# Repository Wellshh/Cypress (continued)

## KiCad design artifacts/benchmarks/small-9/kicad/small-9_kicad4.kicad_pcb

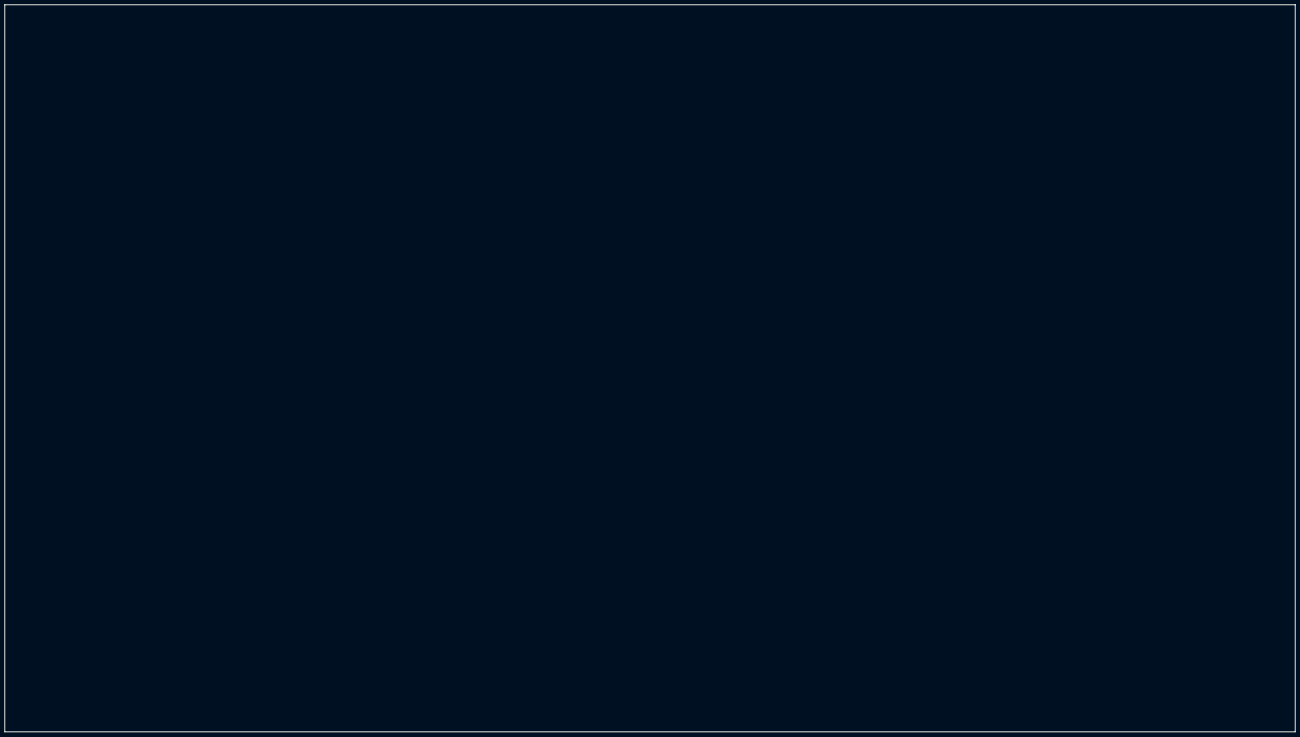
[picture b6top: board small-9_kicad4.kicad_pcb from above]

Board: 2 copper layers, 564.1 x 317.8 mm, 476 parts (0 on the bottom side), 253 nets, no tracks yet.

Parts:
C0: C0; 320-2241-000
C1: C1; 320-2241-000
C2: C2; 320-2241-000
C3: C3; 320-2241-000
C4: C4; 320-2241-000
C5: C5; 320-2241-000
C6: C6; 320-2241-000
C7: C7; 320-2241-000
C8: C8; 320-2241-000
C9: C9; 320-2241-000
C10: C10; 320-2241-000
C11: C11; 320-2241-000
C12: C12; 320-2241-000
C13: C13; 320-2241-000
C14: C14; 032-2145-000
C15: C15; 032-2145-000
C16: C16; 032-2145-000
C17: C17; 032-2145-000
C18: C18; 032-2145-000
C19: C19; 032-2145-000
C20: C20; 032-2145-000
C21: C21; 032-2145-000
C22: C22; 032-2145-000
C23: C23; 032-2145-000
C24: C24; 032-2145-000
C25: C25; 032-2145-000
C26: C26; 032-2145-000
C27: C27; 032-2145-000
C28: C28; 032-2145-000
C29: C29; 032-2145-000
C30: C30; 032-2145-000
C31: C31; 032-2145-000
C32: C32; 032-2145-000
C33: C33; 032-2145-000
C34: C34; 032-2145-000
C35: C35; 032-2145-000
C36: C36; 032-2145-000
C37: C37; 032-2145-000
C38: C38; 032-2145-000
C39: C39; 032-2145-000
C40: C40; 032-2145-000
C41: C41; 032-2145-000
C42: C42; 032-2145-000
C43: C43; 032-2145-000
C44: C44; 032-2145-000
C45: C45; 032-2145-000
C46: C46; 032-2145-000
C47: C47; 032-2145-000
C48: C48; 032-2145-000
C49: C49; 032-2145-000
C50: C50; 032-2145-000
C51: C51; 032-2145-000
C52: C52; 032-2145-000
C53: C53; 032-2145-000
C54: C54; 032-2145-000
C55: C55; 032-2145-000
C56: C56; 032-2145-000
C57: C57; 032-2145-000
C58: C58; 032-2145-000
C59: C59; 032-2145-000
C60: C60; 032-2145-000
C61: C61; 032-2145-000
C62: C62; 032-2145-000
C63: C63; 032-2145-000
C64: C64; 032-2145-000
C65: C65; 032-2145-000
C66: C66; 032-2145-000
C67: C67; 032-2145-000
C68: C68; 032-2145-000
C69: C69; 032-2145-000
C70: C70; 032-2145-000
C71: C71; 032-2145-000
C72: C72; 032-2145-000
C73: C73; 032-2145-000
C74: C74; 032-2145-000
C75: C75; 032-2145-000
C76: C76; 032-2145-000
C77: C77; 032-2145-000
C78: C78; 032-2145-000
C79: C79; 032-2145-000
C80: C80; 032-2145-000
C81: C81; 032-2145-000
C82: C82; 032-2145-000
C83: C83; 032-2145-000
C84: C84; 032-2145-000
C85: C85; 032-2145-000
C86: C86; 032-2145-000
C87: C87; 032-2145-000
C88: C88; 032-2145-000
C89: C89; 032-2145-000
C90: C90; 032-2145-000
C91: C91; 032-2145-000
C92: C92; 032-2145-000
C93: C93; 032-2145-000
C94: C94; 032-2145-000
C95: C95; 032-2145-000
C96: C96; 032-2145-000
C97: C97; 032-2145-000
C98: C98; 032-2145-000
C99: C99; 032-2145-000
C100: C100; 032-2145-000
C101: C101; 032-2145-000
C102: C102; 032-2145-000
C103: C103; 032-2145-000
C104: C104; 032-2145-000
C105: C105; 032-2145-000
C106: C106; 032-2145-000
C107: C107; 032-2145-000
C108: C108; 032-2145-000
C109: C109; 032-2145-000
C110: C110; 032-2145-000
C111: C111; 032-2145-000
C112: C112; 032-2145-000
C113: C113; 032-2145-000
C114: C114; 032-2145-000
C115: C115; 032-2145-000
C116: C116; 032-2145-000
C117: C117; 032-2145-000
C118: C118; 032-2145-000
C119: C119; 032-2145-000
C120: C120; 032-2145-000
C121: C121; 032-2145-000
C122: C122; 032-2145-000
C123: C123; 032-2145-000
C124: C124; 032-2145-000
C125: C125; 032-2145-000
C126: C126; 080-2248-000
C127: C127; 080-2248-000
C128: C128; 080-2248-000
C129: C129; 080-2248-000
C130: C130; 080-2248-000
C131: C131; 080-2248-000
C132: C132; 080-2248-000
C133: C133; 080-2248-000
C134: C134; 080-2248-000
C135: C135; 080-2248-000
C136: C136; 080-2248-000
C137: C137; 080-2248-000
C138: C138; 080-2248-000
C139: C139; 080-2248-000
C140: C140; 130-1487-000
C141: C141; 130-1487-000
C142: C142; 130-1487-000
C143: C143; 130-1487-000
C144: C144; 130-1487-000
C145: C145; 130-1487-000
C146: C146; 130-1487-000
C147: C147; 130-1487-000
C148: C148; 130-1487-000
C149: C149; 130-1487-000
C150: C150; 130-1487-000
C151: C151; 130-1487-000
C152: C152; 130-1487-000
C153: C153; 130-1487-000
C154: C154; 130-1487-000
C155: C155; 130-1487-000
C156: C156; 130-1487-000
C157: C157; 130-1487-000
C158: C158; 130-1487-000
C159: C159; 130-1487-000
C160: C160; 130-1487-000
C161: C161; 130-1487-000
C162: C162; 130-1487-000
C163: C163; 130-1487-000
C164: C164; 130-1487-000
C165: C165; 130-1487-000
C166: C166; 130-1487-000
C167: C167; 130-1487-000
C168: C168; 130-1487-000
C169: C169; 130-1487-000
C170: C170; 130-1487-000
C171: C171; 130-1487-000
C172: C172; 130-1487-000
C173: C173; 130-1487-000
C174: C174; 130-1487-000
C175: C175; 130-1487-000
C176: C176; 130-1487-000
C177: C177; 130-1487-000
C178: C178; 130-1487-000
C179: C179; 130-1487-000
C180: C180; 130-1487-000
C181: C181; 130-1487-000
C182: C182; 130-1487-000
C183: C183; 130-1487-000
C184: C184; 130-1487-000
C185: C185; 130-1487-000
C186: C186; 130-1487-000
C187: C187; 130-1487-000
C188: C188; 130-1487-000
C189: C189; 130-1487-000
C190: C190; 130-1487-000
C191: C191; 130-1487-000
C192: C192; 130-1487-000
C193: C193; 130-1487-000
C194: C194; 130-1487-000
C195: C195; 130-1487-000
C196: C196; 130-1487-000
C197: C197; 130-1487-000
C198: C198; 130-1487-000
C199: C199; 130-1487-000
C200: C200; 130-1487-000
C201: C201; 130-1487-000
C202: C202; 130-1487-000
C203: C203; 130-1487-000
C204: C204; 130-1487-000
C205: C205; 130-1487-000
C206: C206; 130-1487-000
C207: C207; 130-1487-000
C208: C208; 130-1487-000
C209: C209; 130-1487-000
C210: C210; 130-1487-000
C211: C211; 130-1487-000
C212: C212; 130-1487-000
C213: C213; 130-1487-000
C214: C214; 130-1487-000
C215: C215; 130-1487-000
C216: C216; 130-1487-000
C217: C217; 130-1487-000
C218: C218; 130-1487-000
C219: C219; 130-1487-000
C220: C220; 130-1487-000
C221: C221; 130-1487-000
C222: C222; 130-1487-000
C223: C223; 130-1487-000
C224: C224; 032-0863-000
C225: C225; 195-0004-000
C226: C226; 195-0004-000
C227: C227; 195-0004-000
C228: C228; 195-0004-000
C229: C229; 195-0004-000
C230: C230; 195-0004-000
C231: C231; 195-0004-000
C232: C232; 195-0004-000
C233: C233; 195-0004-000
C234: C234; 195-0004-000
C235: C235; 195-0004-000
C236: C236; 195-0004-000
C237: C237; 195-0004-000
C238: C238; 195-0004-000
C239: C239; 195-0004-000
C240: C240; 195-0004-000
C241: C241; 195-0004-000
C242: C242; 195-0004-000
C243: C243; 195-0004-000
C244: C244; 195-0004-000
C245: C245; 195-0004-000
C246: C246; 195-0004-000
C247: C247; 195-0004-000
C248: C248; 195-0004-000
C249: C249; 195-0004-000
C250: C250; 195-0004-000
C251: C251; 195-0004-000
C252: C252; 195-0004-000
C253: C253; 195-0004-000
C254: C254; 195-0004-000
C255: C255; 195-0004-000
C256: C256; 195-0004-000
C257: C257; 195-0004-000
C258: C258; 195-0004-000
C259: C259; 195-0004-000
C260: C260; 195-0004-000
C261: C261; 195-0004-000
C262: C262; 195-0004-000
C263: C263; 195-0004-000
C264: C264; 195-0004-000
C265: C265; 195-0004-000
C266: C266; 195-0004-000
C267: C267; 195-0004-000
C268: C268; 195-0004-000
C269: C269; 195-0004-000
C270: C270; 195-0004-000
C271: C271; 195-0004-000
C272: C272; 195-0004-000
C273: C273; 195-0004-000
C274: C274; 195-0004-000
C275: C275; 195-0004-000
C276: C276; 195-0004-000
C277: C277; 195-0004-000
C278: C278; 195-0004-000
C279: C279; 195-0004-000
C280: C280; 195-0004-000
C281: C281; 195-0005-000
C282: C282; 195-0005-000
C283: C283; 195-0005-000
C284: C284; 195-0005-000
C285: C285; 195-0005-000
C286: C286; 195-0005-000
C287: C287; 195-0005-000
C288: C288; 195-0005-000
C289: C289; 195-0005-000
C290: C290; 195-0005-000
C291: C291; 195-0005-000
C292: C292; 195-0005-000
C293: C293; 195-0005-000
C294: C294; 195-0005-000
C295: C295; 195-0005-000
C296: C296; 195-0005-000
C297: C297; 195-0005-000
C298: C298; 195-0005-000
C299: C299; 195-0005-000
C300: C300; 195-0005-000
C301: C301; 195-0005-000
C302: C302; 195-0005-000
C303: C303; 195-0005-000
C304: C304; 195-0005-000
C305: C305; 195-0005-000
C306: C306; 195-0005-000
C307: C307; 195-0005-000
C308: C308; 195-0005-000
C309: C309; 195-0005-000
C310: C310; 195-0005-000
C311: C311; 195-0005-000
C312: C312; 195-0005-000
C313: C313; 195-0005-000
C314: C314; 195-0005-000
C315: C315; 195-0005-000
C316: C316; 195-0005-000
C317: C317; 195-0005-000
C318: C318; 195-0005-000
C319: C319; 195-0005-000
C320: C320; 195-0005-000
C321: C321; 195-0005-000
C322: C322; 195-0005-000
C323: C323; 195-0005-000
C324: C324; 195-0005-000
C325: C325; 195-0005-000
C326: C326; 195-0005-000
C327: C327; 195-0005-000
C328: C328; 195-0005-000
C329: C329; 195-0005-000
C330: C330; 195-0005-000
C331: C331; 195-0005-000
C332: C332; 195-0005-000
C333: C333; 195-0005-000
C334: C334; 195-0005-000
C335: C335; 195-0005-000
C336: C336; 195-0005-000
C337: C337; 032-0863-000
C338: C338; 032-0863-000
C339: C339; 032-0863-000
C340: C340; 032-0863-000
C341: C341; 032-0863-000
C342: C342; 032-0863-000
C343: C343; 032-0863-000
C344: C344; 032-0863-000
C345: C345; 032-0863-000
C346: C346; 032-0863-000
C347: C347; 032-0863-000
C348: C348; 032-0863-000
C349: C349; 032-0863-000
C350: C350; 032-0863-000
C351: C351; 032-0863-000
C352: C352; 032-0863-000
C353: C353; 032-0863-000
C354: C354; 032-0863-000
C355: C355; 032-0863-000
C356: C356; 032-0863-000
C357: C357; 032-0863-000
C358: C358; 032-0863-000
C359: C359; 032-0863-000
C360: C360; 032-0863-000
C361: C361; 032-0863-000
C362: C362; 032-0863-000
C363: C363; 032-0863-000
C364: C364; 032-0863-000
C365: C365; 032-0863-000
C366: C366; 032-0863-000
C367: C367; 032-0863-000
C368: C368; 032-0863-000
C369: C369; 032-0863-000
C370: C370; 032-0863-000
C371: C371; 032-0863-000
C372: C372; 032-0863-000
C373: C373; 032-0863-000
C374: C374; 032-0863-000
C375: C375; 032-0863-000
C376: C376; 032-0863-000
C377: C377; 032-0863-000
C378: C378; 032-0863-000
C379: C379; 032-0863-000
C380: C380; 032-0863-000
C381: C381; 032-0863-000
C382: C382; 032-0863-000
C383: C383; 032-0863-000
C384: C384; 032-0863-000
C385: C385; 032-0863-000
C386: C386; 032-0863-000
C387: C387; 032-0863-000
C388: C388; 032-0863-000
C389: C389; 032-0863-000
C390: C390; 032-0863-000
C391: C391; 032-0863-000
C392: C392; 032-0863-000
C393: C393; 032-0863-000
C394: C394; 032-0863-000
C395: C395; 032-0863-000
C396: C396; 032-0863-000
C397: C397; 032-0863-000
C398: C398; 032-0863-000
C399: C399; 032-0863-000
C400: C400; 032-0863-000
C401: C401; 032-0863-000
C402: C402; 032-0863-000
C403: C403; 032-0863-000
C404: C404; 032-0863-000
C405: C405; 032-0863-000
C406: C406; 032-0863-000
C407: C407; 032-0863-000
C408: C408; 032-0863-000
C409: C409; 032-0863-000
C410: C410; 032-0863-000
C411: C411; 032-0863-000
C412: C412; 032-0863-000
C413: C413; 032-0863-000
C414: C414; 032-0863-000
C415: C415; 032-0863-000
C416: C416; 032-0863-000
C417: C417; 032-0863-000
C418: C418; 032-0863-000
C419: C419; 032-0863-000
C420: C420; 032-0863-000
C421: C421; 032-0863-000
C422: C422; 032-0863-000
C423: C423; 032-0863-000
C424: C424; 032-0863-000
C425: C425; 032-0863-000
C426: C426; 032-0863-000
C427: C427; 032-0863-000
C428: C428; 032-0863-000
C429: C429; 032-0863-000
C430: C430; 032-0863-000
C431: C431; 032-0863-000
C432: C432; 032-0863-000
C433: C433; 032-0863-000
C434: C434; 032-0863-000
C435: C435; 032-0863-000
C436: C436; 032-0863-000
C437: C437; 032-0863-000
C438: C438; 032-0863-000
C439: C439; 032-0863-000
C440: C440; 032-0863-000
C441: C441; 032-0863-000
C442: C442; 032-0863-000
C443: C443; 195-0337-000
C444: C444; 195-0337-000
C445: C445; 195-0337-000
C446: C446; 195-0337-000
C447: C447; 195-0337-000
C448: C448; 195-0337-000
C449: C449; 195-0337-000
C450: C450; 195-0337-000
C451: C451; 195-0337-000
C452: C452; 195-0337-000
C453: C453; 195-0337-000
C454: C454; 195-0337-000
C455: C455; 195-0337-000
C456: C456; 195-0337-000
C457: C457; 195-0337-000
C458: C458; 195-0337-000
C459: C459; 195-0337-000
C460: C460; 195-0337-000
C461: C461; 195-0337-000
C462: C462; 195-0337-000
C463: C463; 195-0337-000
C464: C464; 195-0337-000
C465: C465; 195-0337-000
C466: C466; 195-0337-000
C467: C467; 195-0337-000
C468: C468; 195-0337-000
C469: C469; 195-0337-000
C470: C470; 195-0337-000
C471: C471; 032-0863-000
C472: C472; 032-0863-000
C473: C473; 032-0863-000
C474: C474; 032-0863-000
C475: C475; 032-0863-000

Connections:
NET_28: C114.1, C128.T30, C128.T68, C215.2, C274.1, C333.1, C335.1, C435.1
NET_29: C117.1, C128.B30, C128.B68, C218.2, C275.1, C334.1, C336.1, C438.1
NET_30: C109.1, C129.B30, C129.B68, C212.2, C271.1, C330.1, C332.1, C430.1
NET_31: C106.1, C129.T30, C129.T68, C209.2, C270.1, C329.1, C331.1, C427.1
NET_32: C98.1, C130.T30, C130.T68, C203.2, C266.1, C325.1, C327.1, C419.1
NET_33: C101.1, C130.B30, C130.B68, C206.2, C267.1, C326.1, C328.1, C422.1
NET_34: C93.1, C131.B30, C131.B68, C200.2, C263.1, C322.1, C324.1, C414.1
NET_35: C90.1, C131.T30, C131.T68, C197.2, C262.1, C321.1, C323.1, C411.1
NET_36: C32.1, C127.T30, C127.T68, C194.2, C258.1, C317.1, C319.1, C471.1
NET_37: C125.1, C127.B30, C127.B68, C221.2, C259.1, C318.1, C320.1, C472.1
NET_38: C27.1, C132.B30, C132.B68, C191.2, C255.1, C314.1, C316.1, C345.1
NET_39: C24.1, C132.T30, C132.T68, C188.2, C254.1, C313.1, C315.1, C342.1
NET_40: C85.1, C126.T30, C126.T68, C182.2, C250.1, C309.1, C311.1, C405.1
NET_41: C88.1, C126.B30, C126.B68, C185.2, C251.1, C310.1, C312.1, C408.1
NET_42: C80.1, C133.B30, C133.B68, C179.2, C247.1, C306.1, C308.1, C400.1
NET_43: C77.1, C133.T30, C133.T68, C140.2, C246.1, C305.1, C307.1, C397.1
NET_44: C69.1, C134.T30, C134.T68, C172.2, C242.1, C301.1, C303.1, C389.1
NET_45: C72.1, C134.B30, C134.B68, C175.2, C243.1, C302.1, C304.1, C392.1
NET_46: C64.1, C135.B30, C135.B68, C169.2, C239.1, C298.1, C300.1, C384.1
NET_47: C61.1, C135.T30, C135.T68, C166.2, C238.1, C297.1, C299.1, C381.1
NET_48: C19.1, C136.T30, C136.T68, C160.2, C234.1, C293.1, C295.1, C374.1
NET_49: C56.1, C136.B30, C136.B68, C163.2, C235.1, C294.1, C296.1, C339.1
NET_50: C17.1, C137.B30, C137.B68, C157.2, C231.1, C290.1, C292.1, C337.1
NET_51: C49.1, C137.T30, C137.T68, C154.2, C230.1, C289.1, C291.1, C368.1
NET_52: C43.1, C138.T30, C138.T68, C148.2, C278.1, C285.1, C287.1, C361.1
NET_53: C46.1, C138.B30, C138.B68, C151.2, C279.1, C286.1, C288.1, C364.1
NET_54: C38.1, C139.B30, C139.B68, C145.2, C226.1, C282.1, C284.1, C356.1
NET_55: C35.1, C139.T30, C139.T68, C142.2, C225.1, C281.1, C283.1, C353.1
NET_92: C116.1, C128.T10, C128.T48, C217.2, C437.1
NET_93: C119.1, C128.B10, C128.B48, C220.2, C440.1
NET_94: C111.1, C129.B10, C129.B48, C214.2, C432.1
NET_95: C108.1, C129.T10, C129.T48, C211.2, C429.1
NET_96: C100.1, C130.T10, C130.T48, C205.2, C421.1
NET_97: C103.1, C130.B10, C130.B48, C208.2, C424.1
NET_98: C95.1, C131.B10, C131.B48, C202.2, C416.1
NET_99: C92.1, C131.T10, C131.T48, C199.2, C413.1
NET_100: C34.1, C127.T10, C127.T48, C196.2, C350.1
NET_101: C123.1, C127.B10, C127.B48, C223.2, C475.1
NET_102: C29.1, C132.B10, C132.B48, C193.2, C347.1
NET_103: C26.1, C132.T10, C132.T48, C190.2, C344.1
NET_104: C87.1, C126.T10, C126.T48, C184.2, C407.1
NET_105: C21.1, C126.B10, C126.B48, C187.2, C410.1
NET_106: C82.1, C133.B10, C133.B48, C181.2, C402.1
NET_107: C79.1, C133.T10, C133.T48, C178.2, C399.1
NET_108: C71.1, C134.T10, C134.T48, C174.2, C391.1
NET_109: C74.1, C134.B10, C134.B48, C177.2, C394.1
NET_110: C66.1, C135.B10, C135.B48, C171.2, C386.1
NET_111: C63.1, C135.T10, C135.T48, C168.2, C383.1
NET_112: C55.1, C136.T10, C136.T48, C162.2, C376.1
NET_113: C58.1, C136.B10, C136.B48, C165.2, C378.1
NET_114: C18.1, C137.B10, C137.B48, C159.2, C338.1
NET_115: C50.1, C137.T10, C137.T48, C156.2, C370.1
NET_116: C45.1, C138.T10, C138.T48, C150.2, C363.1
NET_117: C14.1, C138.B10, C138.B48, C153.2, C224.1
NET_118: C40.1, C139.B10, C139.B48, C147.2, C358.1
NET_119: C37.1, C139.T10, C139.T48, C144.2, C355.1
NET_156: C115.1, C128.T29, C128.T67, C216.2, C436.1
NET_157: C118.1, C128.B29, C128.B67, C219.2, C439.1
NET_158: C110.1, C129.B29, C129.B67, C213.2, C431.1
NET_159: C107.1, C129.T29, C129.T67, C210.2, C428.1
NET_160: C99.1, C130.T29, C130.T67, C204.2, C420.1
NET_161: C102.1, C130.B29, C130.B67, C207.2, C423.1
NET_162: C94.1, C131.B29, C131.B67, C201.2, C415.1
NET_163: C91.1, C131.T29, C131.T67, C198.2, C412.1
NET_164: C33.1, C127.T29, C127.T67, C195.2, C349.1
NET_165: C124.1, C127.B29, C127.B67, C222.2, C474.1
NET_166: C28.1, C132.B29, C132.B67, C192.2, C346.1
NET_167: C25.1, C132.T29, C132.T67, C189.2, C343.1
NET_168: C86.1, C126.T29, C126.T67, C183.2, C406.1
NET_169: C20.1, C126.B29, C126.B67, C186.2, C409.1
NET_170: C81.1, C133.B29, C133.B67, C180.2, C401.1
NET_171: C78.1, C133.T29, C133.T67, C141.2, C398.1
NET_172: C70.1, C134.T29, C134.T67, C173.2, C390.1
NET_173: C73.1, C134.B29, C134.B67, C176.2, C393.1
NET_174: C65.1, C135.B29, C135.B67, C170.2, C385.1
NET_175: C62.1, C135.T29, C135.T67, C167.2, C382.1
NET_176: C54.1, C136.T29, C136.T67, C161.2, C375.1
NET_177: C57.1, C136.B29, C136.B67, C164.2, C377.1
NET_178: C51.1, C137.B29, C137.B67, C158.2, C371.1
NET_179: C16.1, C137.T29, C137.T67, C155.2, C369.1
NET_180: C44.1, C138.T29, C138.T67, C149.2, C362.1
NET_181: C47.1, C138.B29, C138.B67, C152.2, C365.1
NET_182: C39.1, C139.B29, C139.B67, C146.2, C357.1
NET_183: C36.1, C139.T29, C139.T67, C143.2, C354.1
NET_218: C227.1, C228.1, C229.1, C232.1, C233.1, C236.1, C237.1, C240.1, C241.1, C244.1, C245.1, C248.1, C249.1, C252.1, C253.1, C256.1, C257.1, C260.1, C261.1, C264.1, C265.1, C268.1, C269.1, C272.1, C273.1, C276.1, C277.1, C280.1
NET_246: C120.1, C215.1, C216.1, C217.1, C441.1
NET_247: C121.1, C218.1, C219.1, C220.1, C442.1
NET_248: C113.1, C212.1, C213.1, C214.1, C434.1
NET_249: C112.1, C209.1, C210.1, C211.1, C433.1
NET_250: C104.1, C203.1, C204.1, C205.1, C425.1
NET_251: C105.1, C206.1, C207.1, C208.1, C426.1
NET_252: C97.1, C200.1, C201.1, C202.1, C418.1
NET_253: C96.1, C197.1, C198.1, C199.1, C417.1
NET_254: C89.1, C194.1, C195.1, C196.1, C351.1
NET_255: C122.1, C221.1, C222.1, C223.1, C473.1
NET_256: C31.1, C191.1, C192.1, C193.1, C352.1
NET_257: C30.1, C188.1, C189.1, C190.1, C348.1
NET_258: C22.1, C182.1, C183.1, C184.1, C340.1
NET_259: C23.1, C185.1, C186.1, C187.1, C341.1
NET_260: C84.1, C179.1, C180.1, C181.1, C404.1
NET_261: C83.1, C140.1, C141.1, C178.1, C403.1
NET_262: C75.1, C172.1, C173.1, C174.1, C395.1
NET_263: C76.1, C175.1, C176.1, C177.1, C396.1
NET_264: C68.1, C169.1, C170.1, C171.1, C388.1
NET_265: C67.1, C166.1, C167.1, C168.1, C387.1
NET_266: C59.1, C160.1, C161.1, C162.1, C379.1
NET_267: C60.1, C163.1, C164.1, C165.1, C380.1
NET_268: C53.1, C157.1, C158.1, C159.1, C373.1
NET_269: C52.1, C154.1, C155.1, C156.1, C372.1
NET_270: C48.1, C148.1, C149.1, C150.1, C366.1
NET_271: C15.1, C151.1, C152.1, C153.1, C367.1
NET_272: C42.1, C145.1, C146.1, C147.1, C360.1
NET_273: C41.1, C142.1, C143.1, C144.1, C359.1
NET_767: C128.T69, C469.1
NET_768: C128.B69, C470.1
NET_769: C129.B69, C468.1
NET_770: C129.T69, C467.1
NET_771: C130.T69, C465.1
NET_772: C130.B69, C466.1
NET_773: C131.B69, C464.1
NET_774: C131.T69, C463.1
NET_775: C127.T69, C461.1
NET_776: C127.B69, C462.1
NET_777: C132.B69, C460.1
NET_778: C132.T69, C459.1
NET_779: C126.T69, C457.1
NET_780: C126.B69, C458.1
NET_781: C133.B69, C456.1
NET_782: C133.T69, C455.1
NET_783: C134.T69, C453.1
NET_784: C134.B69, C454.1
NET_785: C135.B69, C452.1
NET_786: C135.T69, C451.1
NET_787: C136.T69, C449.1
NET_788: C136.B69, C450.1
NET_789: C137.B69, C448.1
NET_790: C137.T69, C447.1
NET_791: C138.T69, C445.1
NET_792: C138.B69, C446.1
NET_793: C139.B69, C444.1
NET_794: C139.T69, C443.1
NET_898: C128.T28, C274.2
NET_899: C128.B28, C275.2
NET_900: C129.B28, C271.2
NET_901: C129.T28, C270.2
NET_902: C130.T28, C266.2
NET_903: C130.B28, C267.2
NET_904: C131.B28, C263.2
NET_905: C131.T28, C262.2
NET_906: C127.T28, C258.2
NET_907: C127.B28, C259.2
NET_908: C132.B28, C255.2
NET_909: C132.T28, C254.2
NET_910: C126.T28, C250.2
NET_911: C126.B28, C251.2
NET_912: C133.B28, C247.2
NET_913: C133.T28, C246.2
NET_914: C134.T28, C242.2
NET_915: C134.B28, C243.2
NET_916: C135.B28, C239.2
NET_917: C135.T28, C238.2
NET_918: C136.T28, C234.2
NET_919: C136.B28, C235.2
NET_920: C137.B28, C231.2
NET_921: C137.T28, C230.2
NET_922: C138.T28, C278.2
NET_923: C138.B28, C279.2
NET_924: C139.B28, C226.2
NET_925: C139.T28, C225.2
NET_1048: C128.T27, C276.2
NET_1049: C128.B27, C277.2
NET_1050: C129.B27, C273.2
NET_1051: C129.T27, C272.2
NET_1052: C130.T27, C268.2
NET_1053: C130.B27, C269.2
NET_1054: C131.B27, C265.2
NET_1055: C131.T27, C264.2
NET_1056: C127.T27, C260.2
NET_1057: C127.B27, C261.2
NET_1058: C132.B27, C257.2
NET_1059: C132.T27, C256.2
NET_1060: C126.T27, C252.2
NET_1061: C126.B27, C253.2
NET_1062: C133.B27, C249.2
NET_1063: C133.T27, C248.2
NET_1064: C134.T27, C244.2
NET_1065: C134.B27, C245.2
NET_1066: C135.B27, C241.2
NET_1067: C135.T27, C240.2
NET_1068: C136.T27, C236.2
NET_1069: C136.B27, C237.2
NET_1070: C137.B27, C233.2
NET_1071: C137.T27, C232.2
NET_1072: C138.T27, C280.2
NET_1073: C138.B27, C229.2
NET_1074: C139.B27, C228.2
NET_1075: C139.T27, C227.2
NET_3501: C128.T11, C335.2
NET_3502: C128.B11, C336.2
NET_3503: C129.B11, C332.2
NET_3504: C129.T11, C331.2
NET_3505: C130.T11, C327.2
NET_3506: C130.B11, C328.2
NET_3507: C131.B11, C324.2
NET_3508: C131.T11, C323.2
NET_3509: C127.T11, C319.2
NET_3510: C127.B11, C320.2
NET_3511: C132.B11, C316.2
NET_3512: C132.T11, C315.2
NET_3513: C126.T11, C311.2
NET_3514: C126.B11, C312.2
NET_3515: C133.B11, C308.2
NET_3516: C133.T11, C307.2
NET_3517: C134.T11, C303.2
NET_3518: C134.B11, C304.2
NET_3519: C135.B11, C300.2
NET_3520: C135.T11, C299.2
NET_3521: C136.T11, C295.2
NET_3522: C136.B11, C296.2
NET_3523: C137.B11, C292.2
NET_3524: C137.T11, C291.2
NET_3525: C138.T11, C287.2
NET_3526: C138.B11, C288.2
NET_3527: C139.B11, C284.2
NET_3528: C139.T11, C283.2
NET_3565: C128.T12, C333.2
NET_3566: C128.B12, C334.2
NET_3567: C129.B12, C330.2
NET_3568: C129.T12, C329.2
NET_3569: C130.T12, C325.2
NET_3570: C130.B12, C326.2
NET_3571: C131.B12, C322.2
NET_3572: C131.T12, C321.2
NET_3573: C127.T12, C317.2
NET_3574: C127.B12, C318.2
NET_3575: C132.B12, C314.2
NET_3576: C132.T12, C313.2
NET_3577: C126.T12, C309.2
NET_3578: C126.B12, C310.2
NET_3579: C133.B12, C306.2
NET_3580: C133.T12, C305.2
NET_3581: C134.T12, C301.2
NET_3582: C134.B12, C302.2
NET_3583: C135.B12, C298.2
NET_3584: C135.T12, C297.2
NET_3585: C136.T12, C293.2
NET_3586: C136.B12, C294.2
NET_3587: C137.B12, C290.2
NET_3588: C137.T12, C289.2
NET_3589: C138.T12, C285.2
NET_3590: C138.B12, C286.2
NET_3591: C139.B12, C282.2
NET_3592: C139.T12, C281.2
